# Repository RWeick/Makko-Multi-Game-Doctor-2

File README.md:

# Makko-Multi-Game-Doctor-2
An assortment of board files for the Multi Game Doctor 2 (MGD2) as well as the ROM dump from the MGD2. 

Board thicknesses are set in the respective Kicad PCB file.

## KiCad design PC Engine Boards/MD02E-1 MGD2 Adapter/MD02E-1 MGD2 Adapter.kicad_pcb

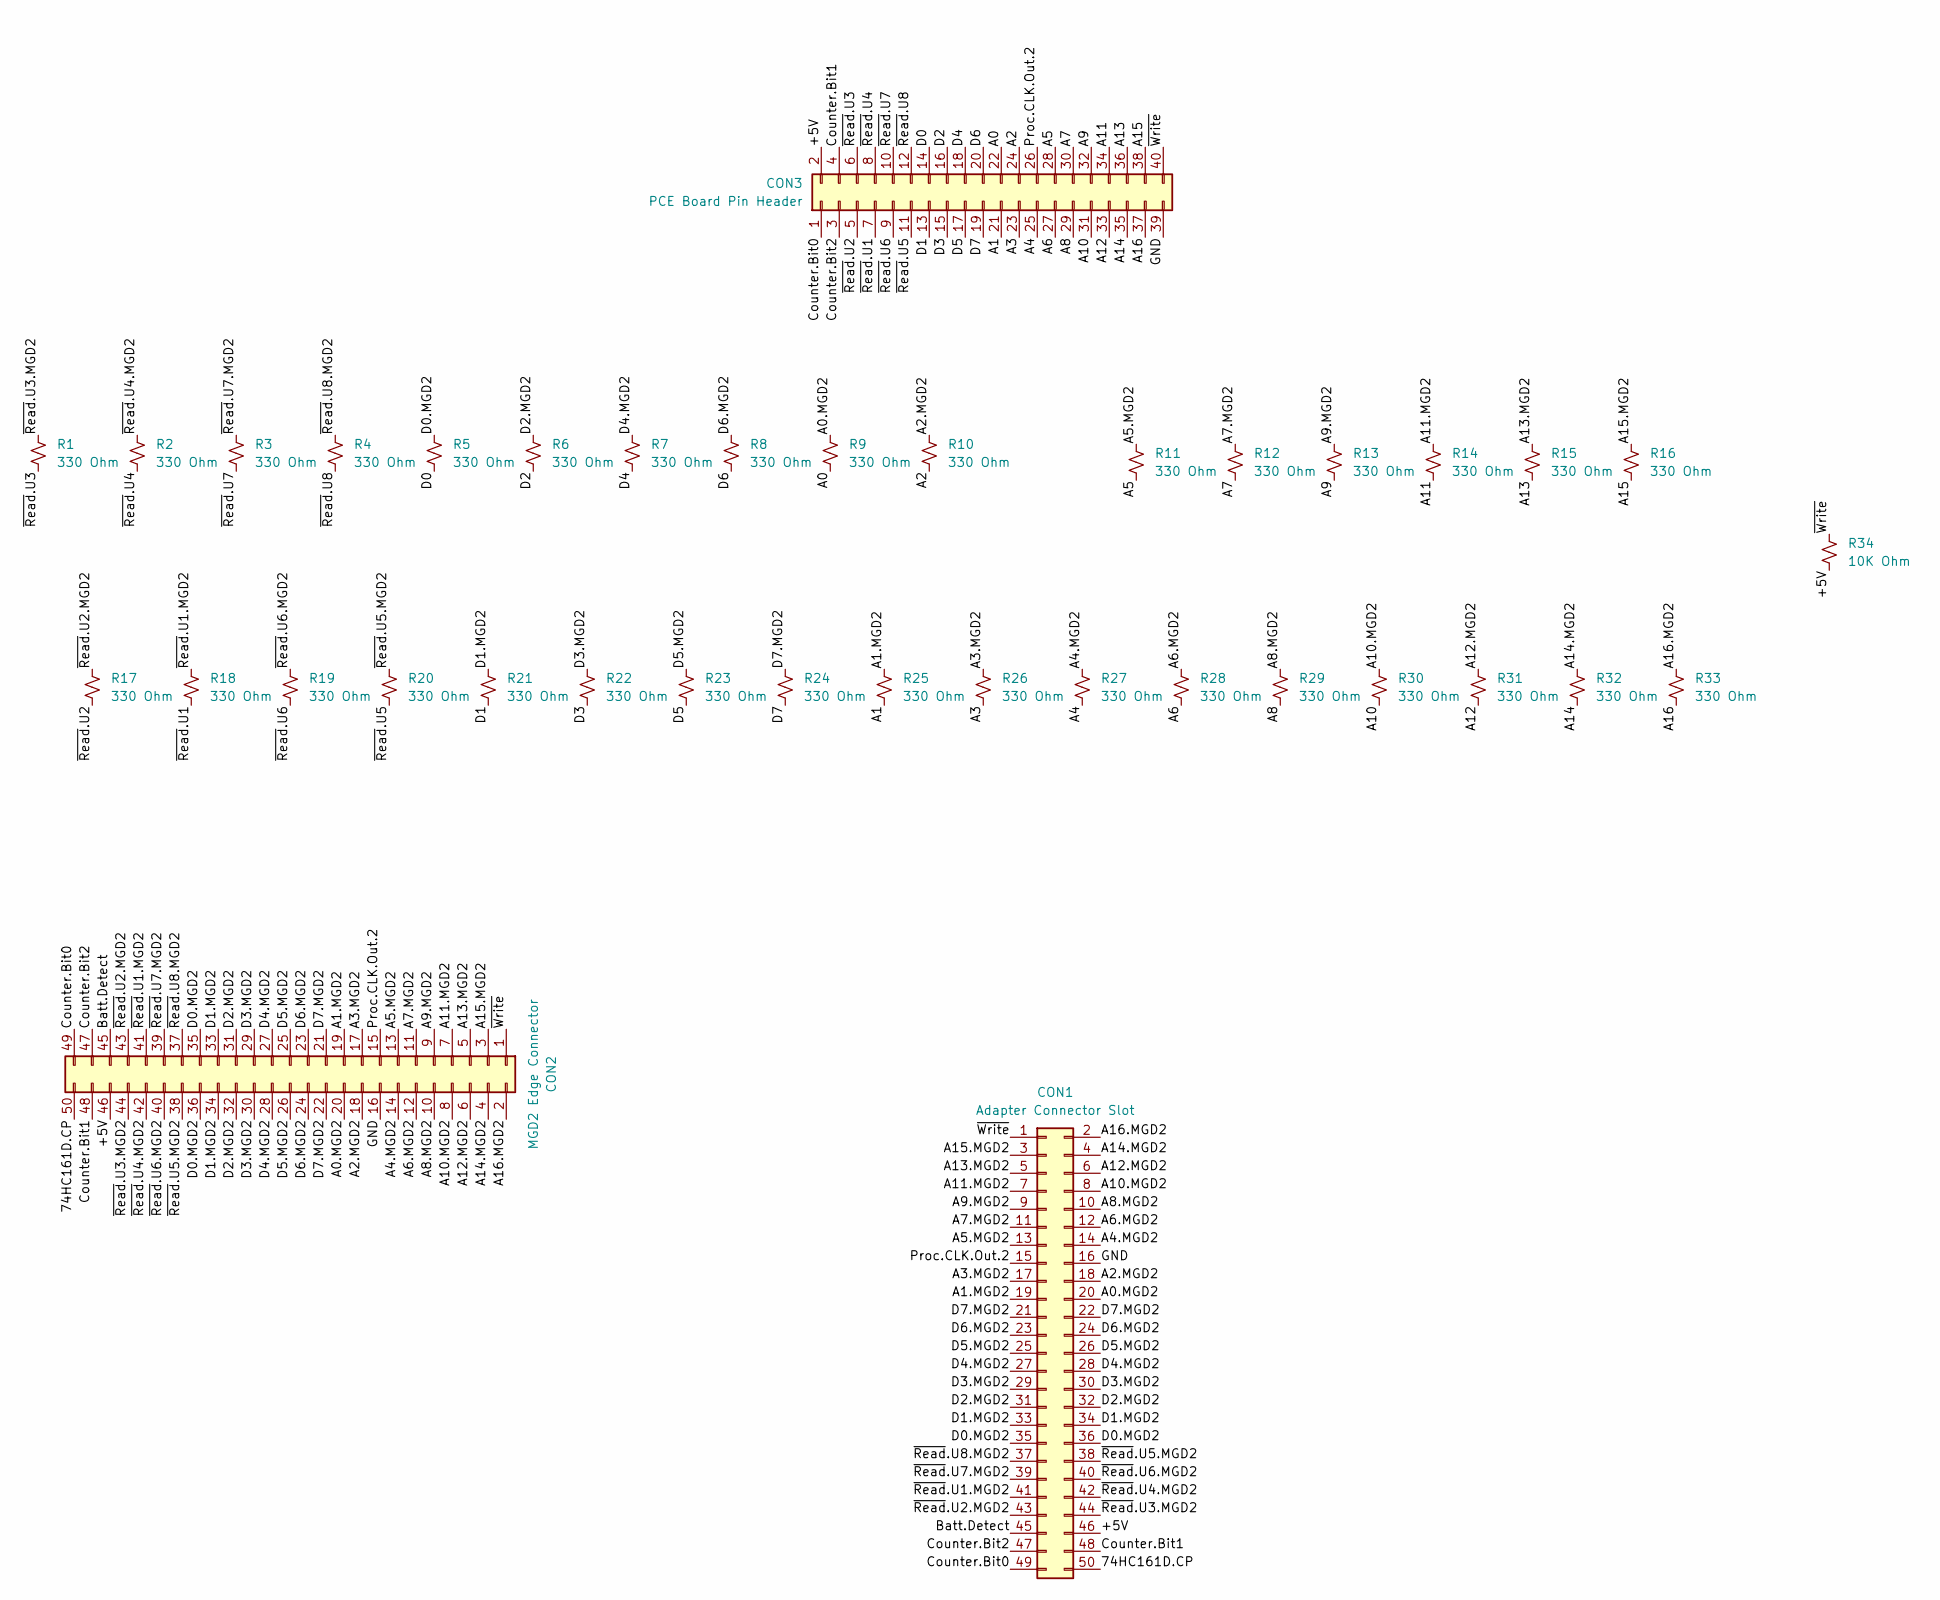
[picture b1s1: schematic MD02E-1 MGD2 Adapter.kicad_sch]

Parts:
CON1: Adapter Connector Slot; J050 Connector
CON2: MGD2 Edge Connector
CON3: PCE Board Pin Header; PinHeader_2x20_P2.00mm_Vertical
R1, R2, R3, R4, R5, R6, R7, R8, R9, R10, R11, R12, R13, R14, R15, R16, R17, R18, R19, R20, R21, R22, R23, R24, R25, R26, R27, R28, R29, R30, R31, R32, R33: 330 Ohm; Resistor
R34: 10K Ohm; Resistor

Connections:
/74HC161D.CP: CON1.50, CON2.50
/+5V: CON1.46, CON2.46, CON3.2, R34.2
/A0: CON3.22, R9.2
/A0.MGD2: CON1.20, CON2.20, R9.1
/A1: CON3.21, R25.2
/A1.MGD2: CON1.19, CON2.19, R25.1
/A2: CON3.24, R10.2
/A2.MGD2: CON1.18, CON2.18, R10.1
/A3: CON3.23, R26.2
/A3.MGD2: CON1.17, CON2.17, R26.1
/A4: CON3.25, R27.2
/A4.MGD2: CON1.14, CON2.14, R27.1
/A5: CON3.28, R11.2
/A5.MGD2: CON1.13, CON2.13, R11.1
/A6: CON3.27, R28.2
/A6.MGD2: CON1.12, CON2.12, R28.1
/A7: CON3.30, R12.2
/A7.MGD2: CON1.11, CON2.11, R12.1
/A8: CON3.29, R29.2
/A8.MGD2: CON1.10, CON2.10, R29.1
/A9: CON3.32, R13.2
/A9.MGD2: CON1.9, CON2.9, R13.1
/A10: CON3.31, R30.2
/A10.MGD2: CON1.8, CON2.8, R30.1
/A11: CON3.34, R14.2
/A11.MGD2: CON1.7, CON2.7, R14.1
/A12: CON3.33, R31.2
/A12.MGD2: CON1.6, CON2.6, R31.1
/A13: CON3.36, R15.2
/A13.MGD2: CON1.5, CON2.5, R15.1
/A14: CON3.35, R32.2
/A14.MGD2: CON1.4, CON2.4, R32.1
/A15: CON3.38, R16.2
/A15.MGD2: CON1.3, CON2.3, R16.1
/A16: CON3.37, R33.2
/A16.MGD2: CON1.2, CON2.2, R33.1
/Batt.Detect: CON1.45, CON2.45
/Counter.Bit0: CON1.49, CON2.49, CON3.1
/Counter.Bit1: CON1.48, CON2.48, CON3.4
/Counter.Bit2: CON1.47, CON2.47, CON3.3
/D0: CON3.14, R5.2
/D0.MGD2: CON1.35, CON1.36, CON2.35, CON2.36, R5.1
/D1: CON3.13, R21.2
/D1.MGD2: CON1.33, CON1.34, CON2.33, CON2.34, R21.1
/D2: CON3.16, R6.2
/D2.MGD2: CON1.31, CON1.32, CON2.31, CON2.32, R6.1
/D3: CON3.15, R22.2
/D3.MGD2: CON1.29, CON1.30, CON2.29, CON2.30, R22.1
/D4: CON3.18, R7.2
/D4.MGD2: CON1.27, CON1.28, CON2.27, CON2.28, R7.1
/D5: CON3.17, R23.2
/D5.MGD2: CON1.25, CON1.26, CON2.25, CON2.26, R23.1
/D6: CON3.20, R8.2
/D6.MGD2: CON1.23, CON1.24, CON2.23, CON2.24, R8.1
/D7: CON3.19, R24.2
/D7.MGD2: CON1.21, CON1.22, CON2.21, CON2.22, R24.1
/GND: CON1.16, CON2.16, CON3.39
/Proc.CLK.Out.2: CON1.15, CON2.15, CON3.26
/~Read.U1: CON3.7, R18.2
/~Read.U1.MGD2: CON1.41, CON2.41, R18.1
/~Read.U2: CON3.5, R17.2
/~Read.U2.MGD2: CON1.43, CON2.43, R17.1
/~Read.U3: CON3.6, R1.2
/~Read.U3.MGD2: CON1.44, CON2.44, R1.1
/~Read.U4: CON3.8, R2.2
/~Read.U4.MGD2: CON1.42, CON2.42, R2.1
/~Read.U5: CON3.11, R20.2
/~Read.U5.MGD2: CON1.38, CON2.38, R20.1
/~Read.U6: CON3.9, R19.2
/~Read.U6.MGD2: CON1.40, CON2.40, R19.1
/~Read.U7: CON3.10, R3.2
/~Read.U7.MGD2: CON1.39, CON2.39, R3.1
/~Read.U8: CON3.12, R4.2
/~Read.U8.MGD2: CON1.37, CON2.37, R4.1
/~Write: CON1.1, CON2.1, CON3.40, R34.1

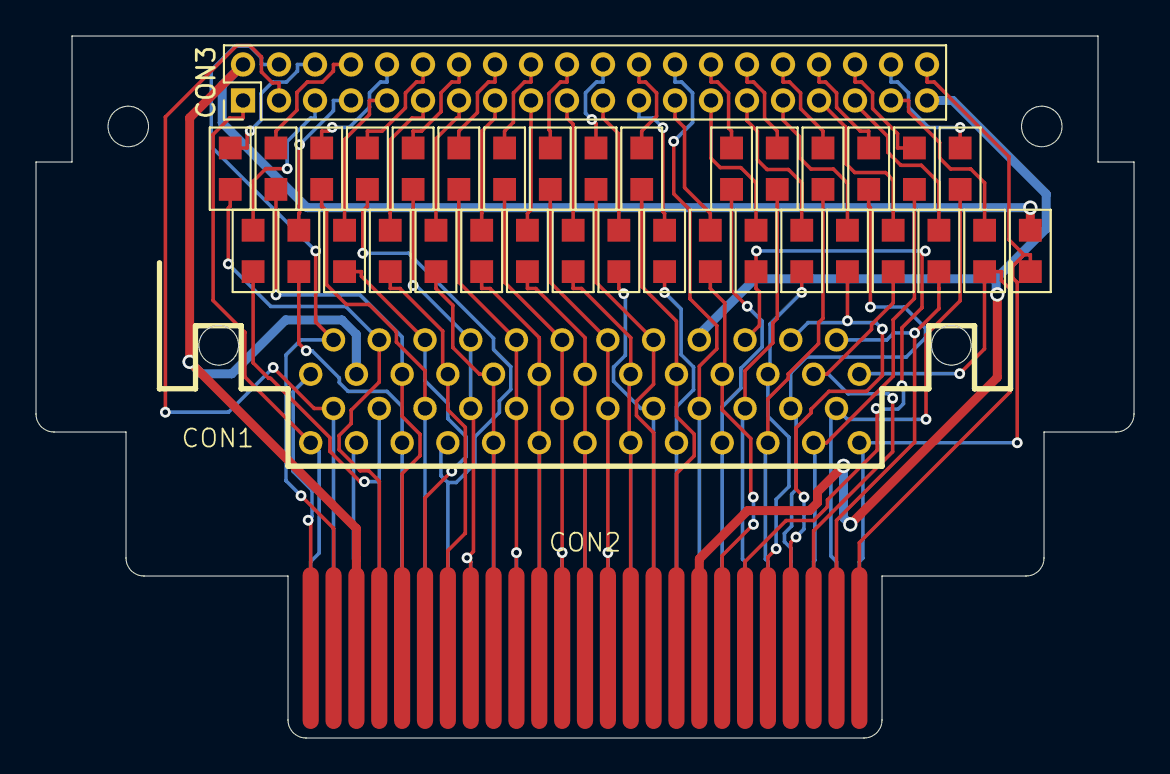
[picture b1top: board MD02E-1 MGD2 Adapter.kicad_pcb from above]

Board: 2 copper layers, 61.0 x 39.0 mm, 37 parts (0 on the bottom side), 75 nets.

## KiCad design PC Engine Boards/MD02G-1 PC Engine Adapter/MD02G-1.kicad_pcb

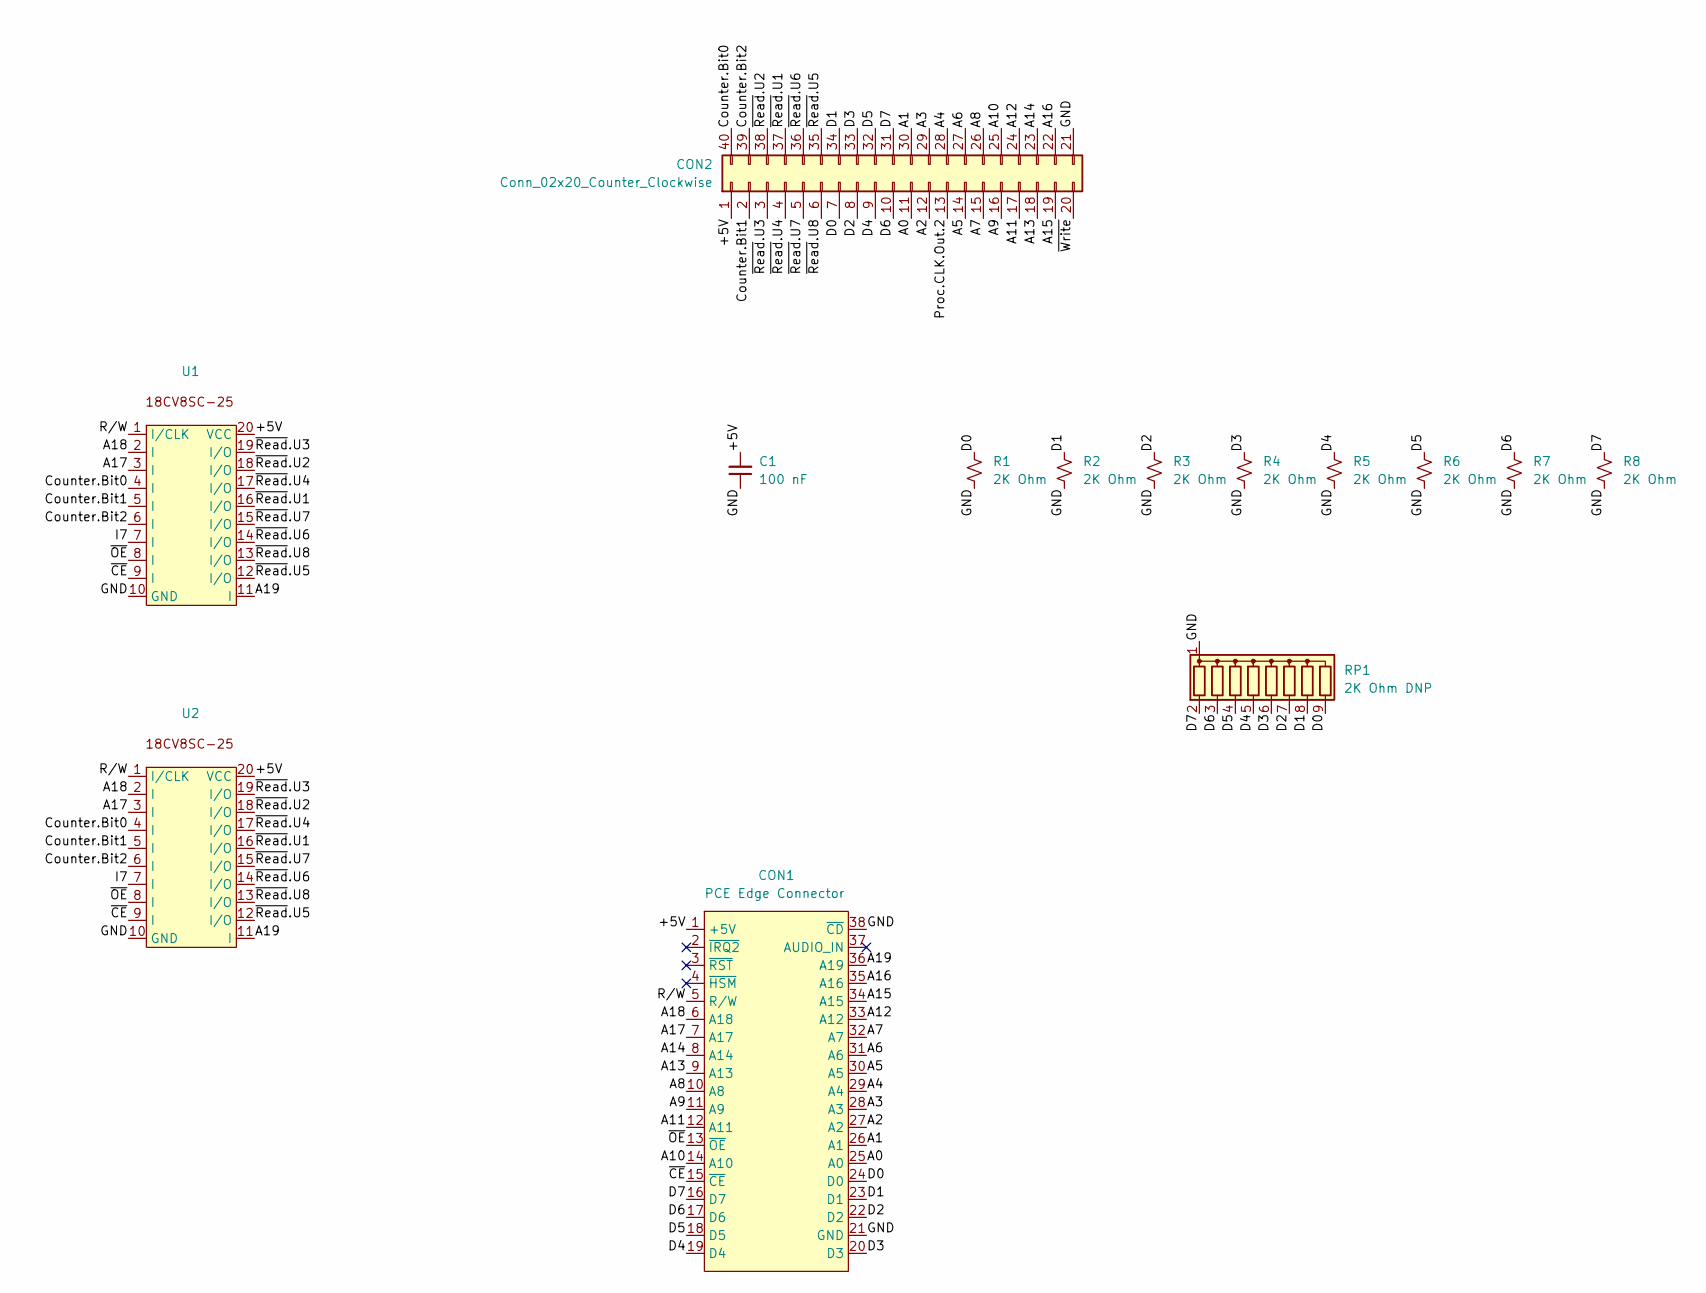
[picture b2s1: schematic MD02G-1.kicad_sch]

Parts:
C1: 100 nF; Capacitor
CON1: PCE Edge Connector; Edge Connector
CON2: Conn_02x20_Counter_Clockwise; PinHeader_2x20_P2.00mm_Vertical
R1, R2, R3, R4, R5, R6, R7, R8: 2K Ohm; Resistor
RP1: 2K Ohm DNP; RP
U1: TSOP-20
U2: SOIC-20

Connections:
/+5V: C1.2, CON1.1 (+5V), CON2.1, U1.20 (VCC), U2.20 (VCC)
/A0: CON1.25 (A0), CON2.11
/A1: CON1.26 (A1), CON2.30
/A2: CON1.27 (A2), CON2.12
/A3: CON1.28 (A3), CON2.29
/A4: CON1.29 (A4), CON2.28
/A5: CON1.30 (A5), CON2.14
/A6: CON1.31 (A6), CON2.27
/A7: CON1.32 (A7), CON2.15
/A8: CON1.10 (A8), CON2.26
/A9: CON1.11 (A9), CON2.16
/A10: CON1.14 (A10), CON2.25
/A11: CON1.12 (A11), CON2.17
/A12: CON1.33 (A12), CON2.24
/A13: CON1.9 (A13), CON2.18
/A14: CON1.8 (A14), CON2.23
/A15: CON1.34 (A15), CON2.19
/A16: CON1.35 (A16), CON2.22
/A17: CON1.7 (A17), U1.3 (I), U2.3 (I)
/A18: CON1.6 (A18), U1.2 (I), U2.2 (I)
/A19: CON1.36 (A19), U1.11 (I), U2.11 (I)
/Counter.Bit0: CON2.40, U1.4 (I), U2.4 (I)
/Counter.Bit1: CON2.2, U1.5 (I), U2.5 (I)
/Counter.Bit2: CON2.39, U1.6 (I), U2.6 (I)
/D0: CON1.24 (D0), CON2.7, R1.1, RP1.9 (R8)
/D1: CON1.23 (D1), CON2.34, R2.1, RP1.8 (R7)
/D2: CON1.22 (D2), CON2.8, R3.1, RP1.7 (R6)
/D3: CON1.20 (D3), CON2.33, R4.1, RP1.6 (R5)
/D4: CON1.19 (D4), CON2.9, R5.1, RP1.5 (R4)
/D5: CON1.18 (D5), CON2.32, R6.1, RP1.4 (R3)
/D6: CON1.17 (D6), CON2.10, R7.1, RP1.3 (R2)
/D7: CON1.16 (D7), CON2.31, R8.1, RP1.2 (R1)
/GND: C1.1, CON1.21 (GND), CON1.38 (~CD), CON2.21, R1.2, R2.2, R3.2, R4.2, R5.2, R6.2, R7.2, R8.2, RP1.1 (common), U1.10 (GND), U2.10 (GND)
/I7: U1.7 (I), U2.7 (I)
/Proc.CLK.Out.2: CON2.13
/R/W: CON1.5 (R/W), U1.1 (I/CLK), U2.1 (I/CLK)
/~CE: CON1.15 (~CE), U1.9 (I), U2.9 (I)
/~OE: CON1.13 (~OE), U1.8 (I), U2.8 (I)
/~Read.U1: CON2.37, U1.16 (I/O), U2.16 (I/O)
/~Read.U2: CON2.38, U1.18 (I/O), U2.18 (I/O)
/~Read.U3: CON2.3, U1.19 (I/O), U2.19 (I/O)
/~Read.U4: CON2.4, U1.17 (I/O), U2.17 (I/O)
/~Read.U5: CON2.35, U1.12 (I/O), U2.12 (I/O)
/~Read.U6: CON2.36, U1.14 (I/O), U2.14 (I/O)
/~Read.U7: CON2.5, U1.15 (I/O), U2.15 (I/O)
/~Read.U8: CON2.6, U1.13 (I/O), U2.13 (I/O)
/~Write: CON2.20

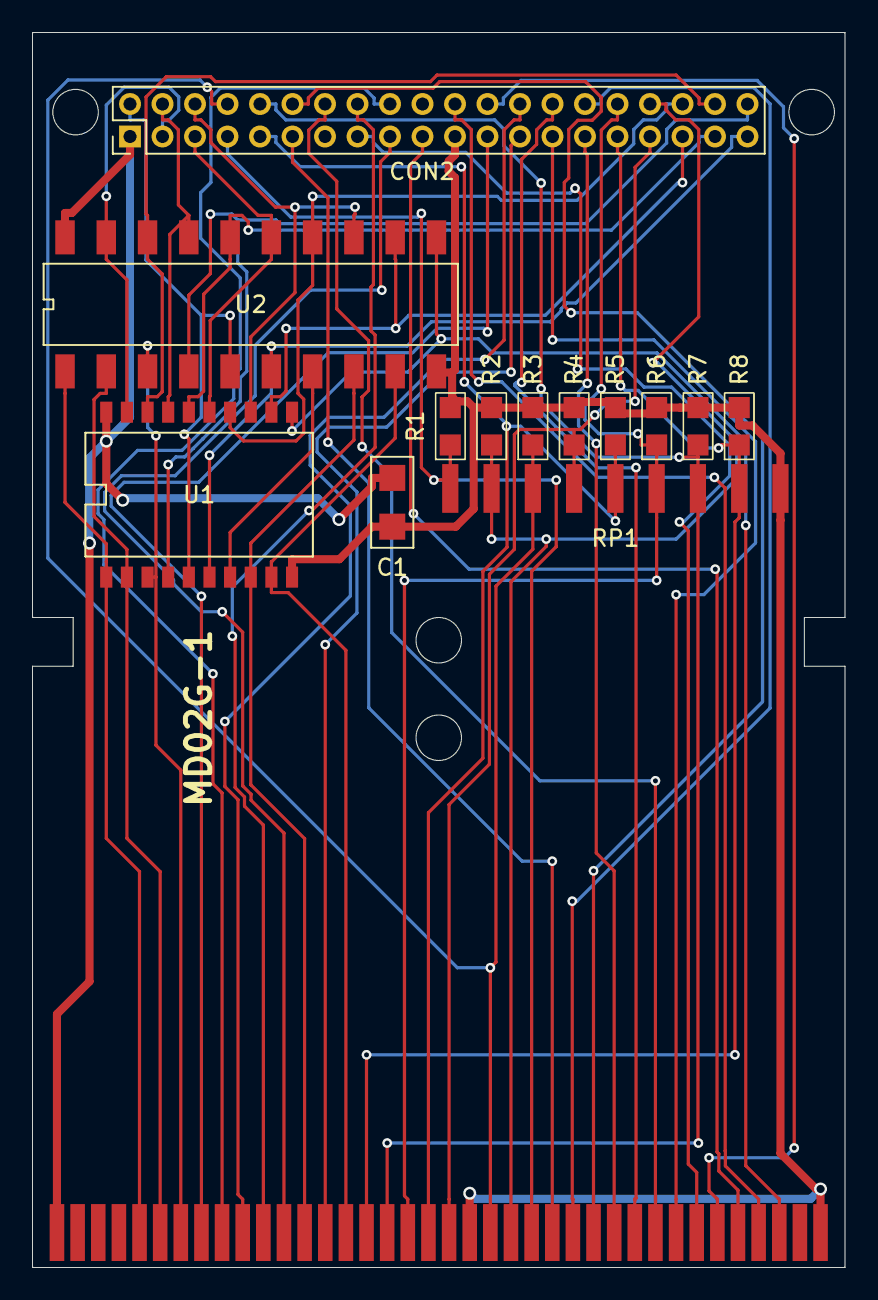
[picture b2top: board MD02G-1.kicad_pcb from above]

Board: 2 copper layers, 50.0 x 76.0 mm, 14 parts (0 on the bottom side), 45 nets.

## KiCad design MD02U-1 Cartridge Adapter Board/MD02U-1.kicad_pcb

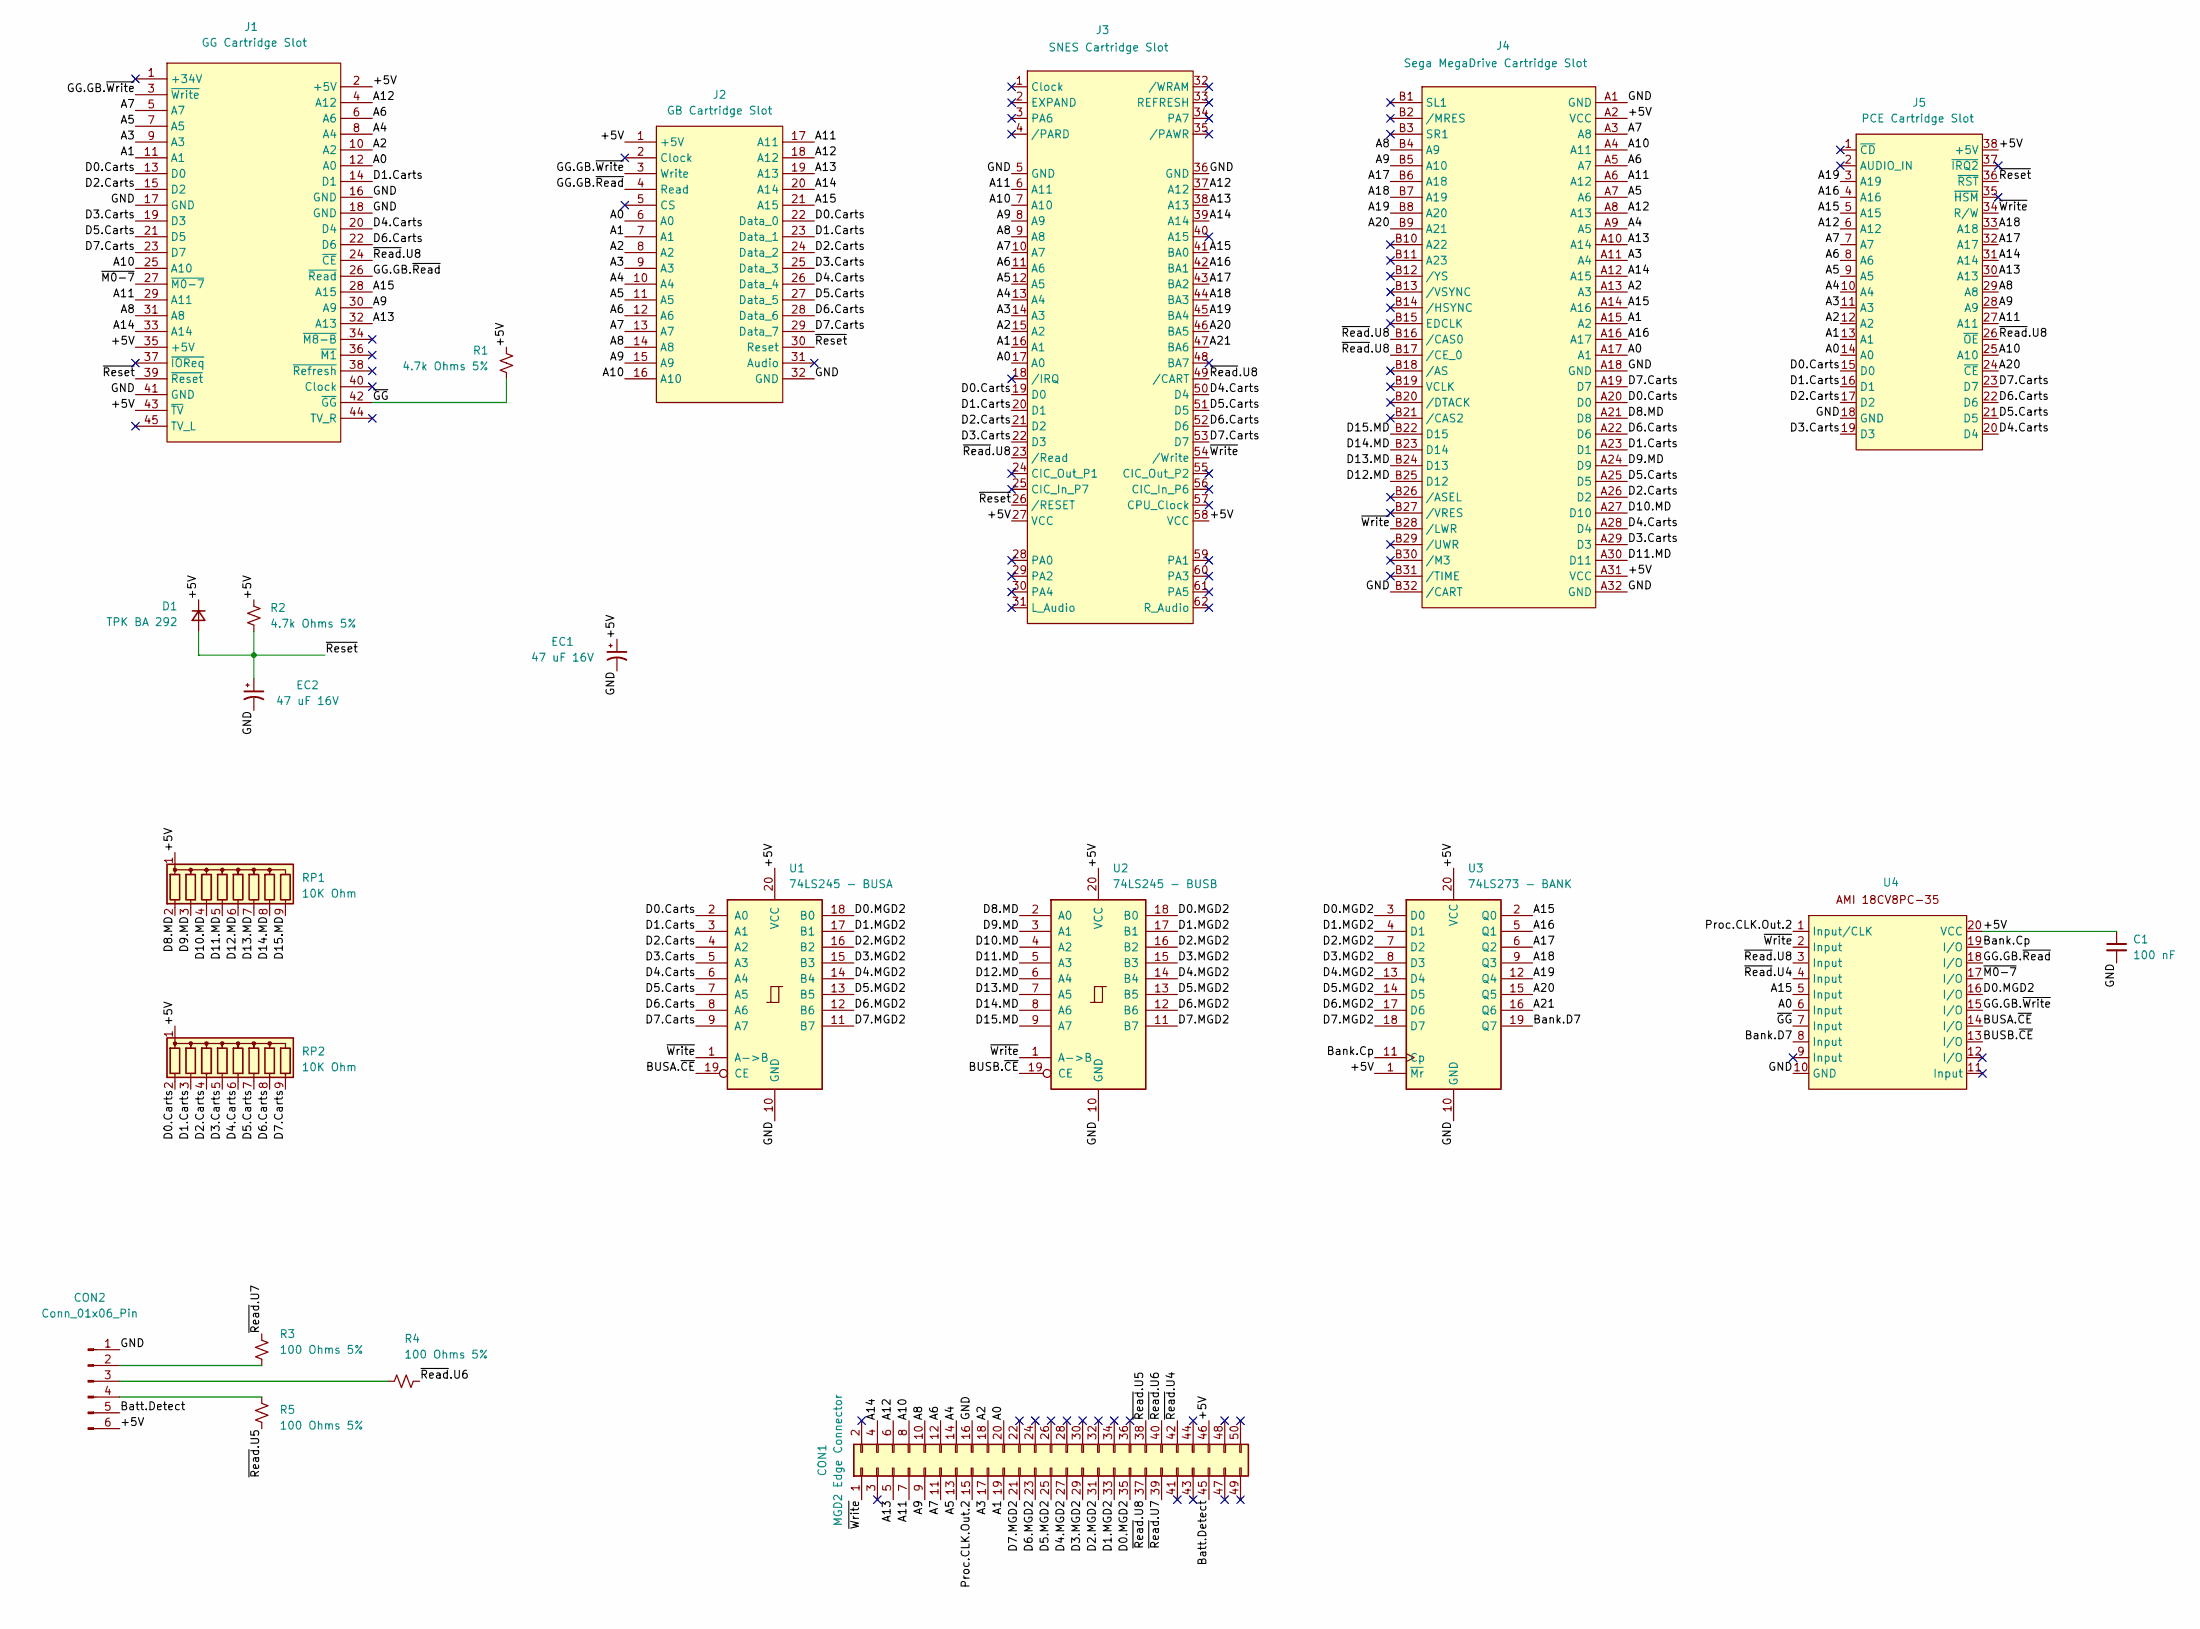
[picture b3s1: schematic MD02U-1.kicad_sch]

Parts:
C1: 100 nF; C_Disc_D5.0mm_W2.5mm_P5.00mm
CON1: MGD2 Edge Connector
CON2: Conn_01x06_Pin; PinHeader_1x06_P2.54mm_Vertical
D1: TPK BA 292; D_A-405_P7.62mm_Horizontal
EC1, EC2: 47 uF 16V; CP_Radial_D5.0mm_P2.50mm
J1: GG Cartridge Slot
J2: GB Cartridge Slot
J3: SNES Cartridge Slot
J4: Sega MegaDrive Cartridge Slot; MD Cartridge Slot
J5: PCE Cartridge Slot; PCE Edge Connector
R1, R2: 4.7k Ohms 5%; THT Resistor
R3, R4, R5: 100 Ohms 5%; THT Resistor
RP1, RP2: 10K Ohm; R_Array_SIP9
U1: 74LS245 - BUSA; DIP-20_W7.62mm_Socket
U2: 74LS245 - BUSB; DIP-20_W7.62mm_Socket
U3: 74LS273 - BANK; DIP-20_W7.62mm_Socket
U4: DIP-20_W7.62mm_Socket

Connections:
/+5V: C1.1, CON1.46, CON2.6, D1.1 (K), EC1.1, J1.2 (+5V), J1.35 (+5V), J1.43 (~TV), J2.1 (+5V), J3.27 (VCC), J3.58 (VCC), J4.A2 (VCC), J4.A31 (VCC), J5.38 (+5V), R1.2, R2.1, RP1.1 (common), RP2.1 (common), U1.20 (VCC), U2.20 (VCC), U3.1 (~Mr), U3.20 (VCC), U4.20 (VCC)
/A0: CON1.20, J1.12 (A0), J2.6 (A0), J3.17 (A0), J4.A17 (A1), J5.14 (A0), U4.6 (Input)
/A1: CON1.19, J1.11 (A1), J2.7 (A1), J3.16 (A1), J4.A15 (A2), J5.13 (A1)
/A2: CON1.18, J1.10 (A2), J2.8 (A2), J3.15 (A2), J4.A13 (A3), J5.12 (A2)
/A3: CON1.17, J1.9 (A3), J2.9 (A3), J3.14 (A3), J4.A11 (A4), J5.11 (A3)
/A4: CON1.14, J1.8 (A4), J2.10 (A4), J3.13 (A4), J4.A9 (A5), J5.10 (A4)
/A5: CON1.13, J1.7 (A5), J2.11 (A5), J3.12 (A5), J4.A7 (A6), J5.9 (A5)
/A6: CON1.12, J1.6 (A6), J2.12 (A6), J3.11 (A6), J4.A5 (A7), J5.8 (A6)
/A7: CON1.11, J1.5 (A7), J2.13 (A7), J3.10 (A7), J4.A3 (A8), J5.7 (A7)
/A8: CON1.10, J1.31 (A8), J2.14 (A8), J3.9 (A8), J4.B4 (A9), J5.29 (A8)
/A9: CON1.9, J1.30 (A9), J2.15 (A9), J3.8 (A9), J4.B5 (A10), J5.28 (A9)
/A10: CON1.8, J1.25 (A10), J2.16 (A10), J3.7 (A10), J4.A4 (A11), J5.25 (A10)
/A11: CON1.7, J1.29 (A11), J2.17 (A11), J3.6 (A11), J4.A6 (A12), J5.27 (A11)
/A12: CON1.6, J1.4 (A12), J2.18 (A12), J3.37 (A12), J4.A8 (A13), J5.6 (A12)
/A13: CON1.5, J1.32 (A13), J2.19 (A13), J3.38 (A13), J4.A10 (A14), J5.30 (A13)
/A14: CON1.4, J1.33 (A14), J2.20 (A14), J3.39 (A14), J4.A12 (A15), J5.31 (A14)
/A15: J1.28 (A15), J2.21 (A15), J3.41 (BA0), J4.A14 (A16), J5.5 (A15), U3.2 (Q0), U4.5 (Input)
/A16: J3.42 (BA1), J4.A16 (A17), J5.4 (A16), U3.5 (Q1)
/A17: J3.43 (BA2), J4.B6 (A18), J5.32 (A17), U3.6 (Q2)
/A18: J3.44 (BA3), J4.B7 (A19), J5.33 (A18), U3.9 (Q3)
/A19: J3.45 (BA4), J4.B8 (A20), J5.3 (A19), U3.12 (Q4)
/A20: J3.46 (BA5), J4.B9 (A21), J5.24 (~CE), U3.15 (Q5)
/A21: J3.47 (BA6), U3.16 (Q6)
/BUSA.~CE: U1.19 (CE), U4.14 (I/O)
/BUSB.~CE: U2.19 (CE), U4.13 (I/O)
/Bank.Cp: U3.11 (Cp), U4.19 (I/O)
/Bank.D7: U3.19 (Q7), U4.8 (Input)
/Batt.Detect: CON1.45, CON2.5
/D0.Carts: J1.13 (D0), J2.22 (Data_0), J3.19 (D0), J4.A20 (D0), J5.15 (D0), RP2.2 (R1), U1.2 (A0)
/D0.MGD2: CON1.35, U1.18 (B0), U2.18 (B0), U3.3 (D0), U4.16 (I/O)
/D1.Carts: J1.14 (D1), J2.23 (Data_1), J3.20 (D1), J4.A23 (D1), J5.16 (D1), RP2.3 (R2), U1.3 (A1)
/D1.MGD2: CON1.33, U1.17 (B1), U2.17 (B1), U3.4 (D1)
/D2.Carts: J1.15 (D2), J2.24 (Data_2), J3.21 (D2), J4.A26 (D2), J5.17 (D2), RP2.4 (R3), U1.4 (A2)
/D2.MGD2: CON1.31, U1.16 (B2), U2.16 (B2), U3.7 (D2)
/D3.Carts: J1.19 (D3), J2.25 (Data_3), J3.22 (D3), J4.A29 (D3), J5.19 (D3), RP2.5 (R4), U1.5 (A3)
/D3.MGD2: CON1.29, U1.15 (B3), U2.15 (B3), U3.8 (D3)
/D4.Carts: J1.20 (D4), J2.26 (Data_4), J3.50 (D4), J4.A28 (D4), J5.20 (D4), RP2.6 (R5), U1.6 (A4)
/D4.MGD2: CON1.27, U1.14 (B4), U2.14 (B4), U3.13 (D4)
/D5.Carts: J1.21 (D5), J2.27 (Data_5), J3.51 (D5), J4.A25 (D5), J5.21 (D5), RP2.7 (R6), U1.7 (A5)
/D5.MGD2: CON1.25, U1.13 (B5), U2.13 (B5), U3.14 (D5)
/D6.Carts: J1.22 (D6), J2.28 (Data_6), J3.52 (D6), J4.A22 (D6), J5.22 (D6), RP2.8 (R7), U1.8 (A6)
/D6.MGD2: CON1.23, U1.12 (B6), U2.12 (B6), U3.17 (D6)
/D7.Carts: J1.23 (D7), J2.29 (Data_7), J3.53 (D7), J4.A19 (D7), J5.23 (D7), RP2.9 (R8), U1.9 (A7)
/D7.MGD2: CON1.21, U1.11 (B7), U2.11 (B7), U3.18 (D7)
/D8.MD: J4.A21 (D8), RP1.2 (R1), U2.2 (A0)
/D9.MD: J4.A24 (D9), RP1.3 (R2), U2.3 (A1)
/D10.MD: J4.A27 (D10), RP1.4 (R3), U2.4 (A2)
/D11.MD: J4.A30 (D11), RP1.5 (R4), U2.5 (A3)
/D12.MD: J4.B25 (D12), RP1.6 (R5), U2.6 (A4)
/D13.MD: J4.B24 (D13), RP1.7 (R6), U2.7 (A5)
/D14.MD: J4.B23 (D14), RP1.8 (R7), U2.8 (A6)
/D15.MD: J4.B22 (D15), RP1.9 (R8), U2.9 (A7)
/GG.GB.~Read: J1.26 (~Read), J2.4 (Read), U4.18 (I/O)
/GG.GB.~Write: J1.3 (~Write), J2.3 (Write), U4.15 (I/O)
/GND: C1.2, CON1.16, CON2.1, EC1.2, EC2.2, J1.16 (GND), J1.17 (GND), J1.18 (GND), J1.41 (GND), J2.32 (GND), J3.5 (GND), J3.36 (GND), J4.A1 (GND), J4.A18 (GND), J4.A32 (GND), J4.B32 (/CART), J5.18 (GND), U1.10 (GND), U2.10 (GND), U3.10 (GND), U4.10 (GND)
/Proc.CLK.Out.2: CON1.15, U4.1 (Input/CLK)
/~GG: J1.42 (~GG), R1.1, U4.7 (Input)
/~M0-7: J1.27 (~M0-7), U4.17 (I/O)
/~Read.U4: CON1.42, U4.4 (Input)
/~Read.U5: CON1.38, R5.2
/~Read.U6: CON1.40, R4.2
/~Read.U7: CON1.39, R3.2
/~Read.U8: CON1.37, J1.24 (~CE), J3.23 (/Read), J3.49 (/CART), J4.B16 (/CAS0), J4.B17 (/CE_0), J5.26 (~OE), U4.3 (Input)
/~Reset: D1.2 (A), EC2.1, J1.39 (~Reset), J2.30 (Reset), J3.26 (/RESET), J5.36 (~RST), R2.2
/~Write: CON1.1, J3.54 (/Write), J4.B28 (/LWR), J5.34 (R/W), U1.1 (A->B), U2.1 (A->B), U4.2 (Input)
unnamed: CON2.2, R3.1
unnamed: CON2.3, R4.1
unnamed: CON2.4, R5.1

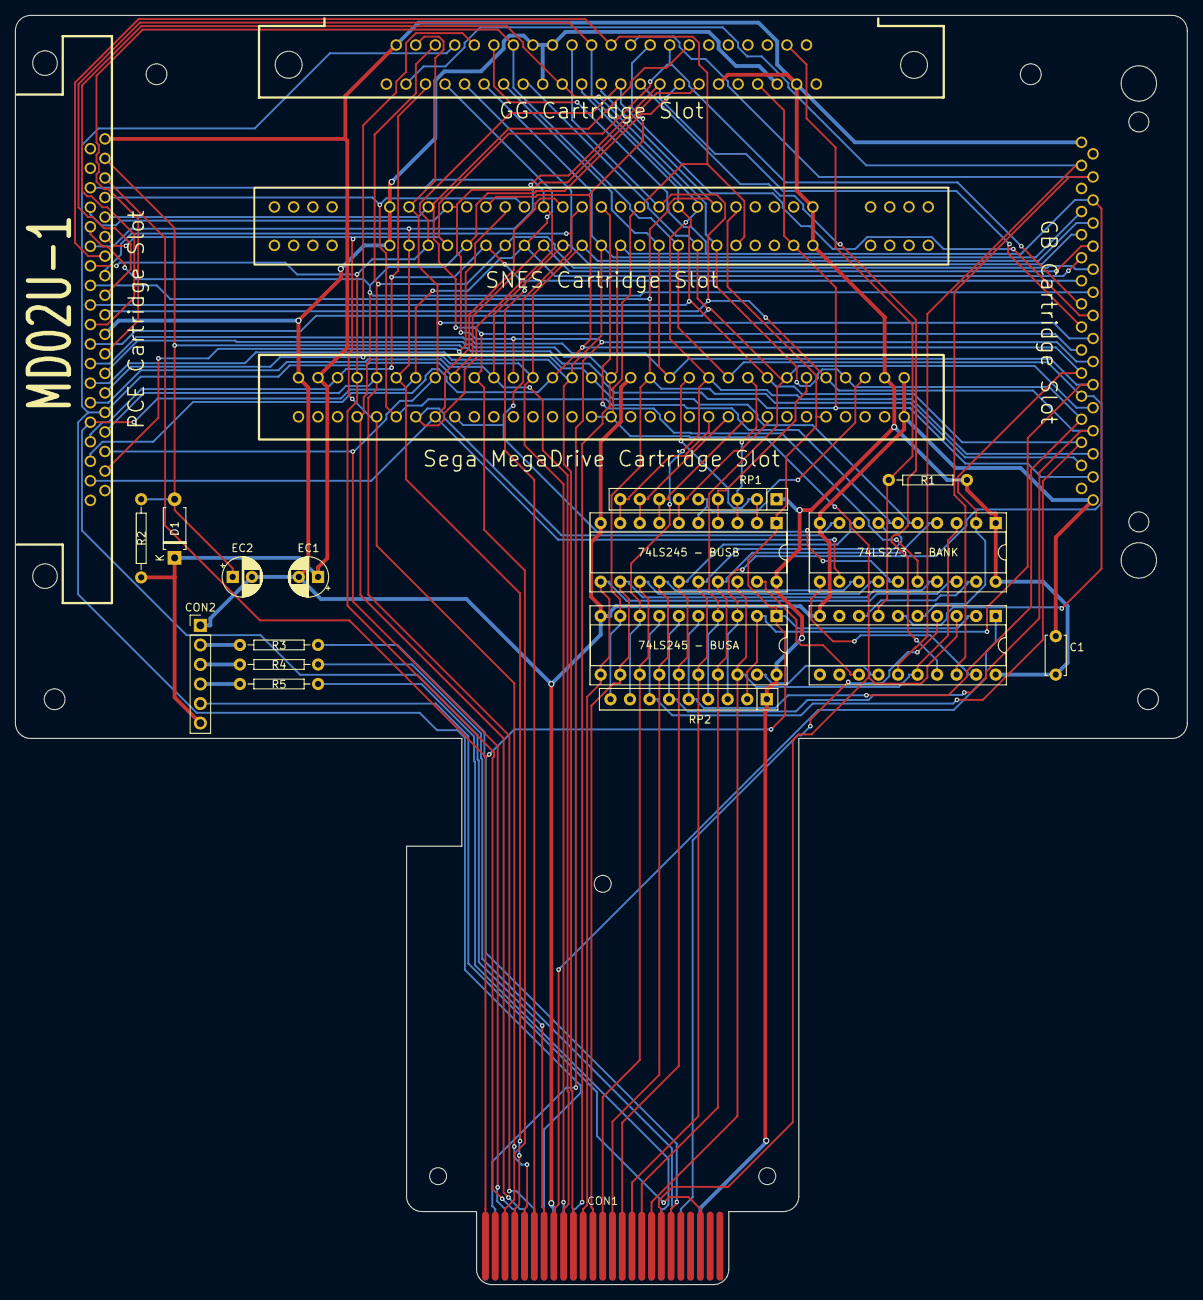
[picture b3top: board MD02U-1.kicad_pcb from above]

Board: 2 copper layers, 152.4 x 165.0 mm, 22 parts (0 on the bottom side), 68 nets.
